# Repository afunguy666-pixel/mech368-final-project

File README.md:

# MECH 368 mobile robot starter

[中文版 / Chinese](README.zh-CN.md)

The direct-wired car uses four reflectance sensors on A0–A3, two LM393 obstacle
inputs and a DRV8833. Two Nano 33 BLE Sense Rev2 boards run `firmware/robot`
and `firmware/remote`. The remote sends heartbeats and accepts `e` over USB
serial to request an E-stop. With a fresh link, swipe UP on the car to calibrate
and start. After an E-stop, any new swipe on the car clears the latch. Wait for
a fresh heartbeat and swipe UP to drive. DOWN stops active navigation locally.

The remote forwards 10 Hz pose telemetry to a receive-only Windows recorder. An
optional normally-open handheld stop button connects D2 to ground. Build the
paired sketches with the project compile script for credit-aware BLE writes.
[Recorder, teach/live examples and bench results (Chinese)](docs/TELEMETRY.zh-CN.md)
· [Tilt steering, low-battery LED and heat map (Chinese)](docs/GESTURE_BATTERY_HEATMAP.zh-CN.md)

See [BLE protocol and bench checklist](docs/BLE_PROTOCOL.md) for the exact wire
format, timing, setup API blocking limitations and unperformed hardware tests.

| Path | Purpose |
| --- | --- |
| `firmware/robot/` | Direct-wired autonomous car, BLE watchdog, local recovery and motor enable |
| `firmware/remote/` | Remote sketch; integration point for pose estimation, BLE, and the E-stop request |
| `libraries/Mech368BLE/` | Portable packet codec, receiver and remote ACK tracking |
| `libraries/Mech368Safety/` | Portable state machine shared with the host test |
| `libraries/Mech368Line/` | Portable IR sensing, navigation, kinematics and odometry |
| `libraries/Mech368Tracker/` | Nano sensor and motor adapter shared by the car and standalone example. [Wiring and tuning](docs/LINE_FOLLOWING.md) |
| `tests/` | Deterministic host assertions for watchdog and E-stop behavior |
| `.github/workflows/ci.yml` | Independent host-test, firmware-simulator and board-compile jobs; no uploads to boards |

## Run locally

On Linux/macOS, or in a Windows Bash environment with the tools on PATH:

```sh
bash scripts/test-host.sh

# Requires Arduino CLI 1.3.1 on PATH (same toolchain CI uses).
arduino-cli core update-index
arduino-cli core install arduino:mbed_nano@4.6.0
arduino-cli lib install ArduinoBLE@2.1.1 Arduino_APDS9960@1.0.4 Arduino_BMI270_BMM150@1.2.4
bash scripts/compile-firmware.sh
```

The host test requires a C++11 compiler; set `CXX` if necessary. Compile only:
neither script flashes hardware. Arduino's [Rev2 manual](https://docs.arduino.cc/tutorials/nano-33-ble-sense-rev2/cheat-sheet/)
identifies the Mbed OS Nano package. The build target is `arduino:mbed_nano:nano33ble`.

## Implement and verify on the bench

1. **BLE and pose steering.** Verify the two actual boards and confirm which
   endpoint advertises. Measure BLE processing latency, including synchronous setup calls. Map
   calibrated remote roll and pitch to linear and angular velocity. Review the implemented
   command units, bounds, packet format and sequence/session handling. Validate
   type, size, version, bounds, and freshness before refreshing the watchdog;
   cached, malformed, duplicated or stale packets must not extend it. Treat
   reported disconnects immediately, and implement the required link-loss LED on
   each device (including detection of a stale peer on the remote).
2. **Motor inhibition and timing.** The state machine expires at 450 ms after
   the last new valid motion packet, leaving 50 ms for scheduling and output
   latency. That is not a hardware timing claim. With motors electrically
   isolated first, capture the last accepted packet and verified zero/disable
   output and demonstrate an end-to-end delay no longer than 500 ms under
   worst observed polling load. Test no packets at startup, packet silence,
   invalid traffic, abrupt disconnect and reconnect. Confirm actual motor
   driver polarity, disable behavior and electrical defaults before connecting
   motor power. All drive modes must share the same output gate.
3. **Emergency stop.** Show that a valid remote E-stop takes precedence over
   motion and a simultaneous recovery gesture, stays latched across a
   disconnect, and ignores further drive commands. Generate a new local
   APDS-9960 gesture event to clear the latch; confirm motion is still blocked
   until another good command arrives after recovery. The latch here is
   RAM-only. Verify startup/reset leaves physical outputs disabled; define
   a deliberate re-arm strategy before allowing motors to operate after reset.
4. **Remaining course hardware.** Verify the well-marked low-battery
   indicator and its threshold on your pack. Characterize wheel direction
   and encoder scaling, validate differential steering, and then test IR
   track following, obstacle avoidance, IMU/odometry pose tracking, and mapping
   against the course handout. Start motor tests with wheels clear of the
   bench and a safe independent means to cut power. Log measurements and
   observed behavior rather than treating compilation as acceptance.

## Firmware-in-the-loop simulator

Run the **unmodified** `robot.ino` and `remote.ino` on two virtual boards with a
simulated BLE radio, plus a virtual vehicle (motors, encoders, line sensors,
ultrasonic, IMU, gestures, battery, temperature) on the handout's field map, using only Bash and a
C++17 compiler:

```sh
bash scripts/run-fw-sim.sh                   # all scenarios
bash scripts/run-fw-sim.sh estop_latch       # one scenario with full log
bash scripts/run-fw-sim.sh --seeds 20 link_stability
```

Each run writes an interactive HTML replay plus CSV/log files to `build/fwsim/`.
Wiring, geometry and the course are text files in `sim/vehicles/` and
`sim/worlds/`; scenarios are C++ files in `sim/fwsim/scenarios/`. See
[docs/SIMULATOR.md](docs/SIMULATOR.md) for the API, the models, their limits,
and the current findings on the Phase 1 link timing.

| Path | Purpose |
| --- | --- |
| `sim/fwsim/hostduino/` | Host stand-ins for Arduino core, ArduinoBLE, BMI270/BMM150 IMU, APDS-9960, HS300x |
| `sim/fwsim/` | Virtual boards, radio, vehicle/world models, replay viewer, scenarios |
| `sim/examples/line_follower/` | Demo sketch (not course firmware) driving the virtual vehicle |
| `sim/examples/line_tracker/` | Standalone navigation example. Use `robot_track_cones` to exercise both course sketches together. |

## Software-in-the-loop (SIL) simulator

Run the host tests and generate five CSV traces without an Arduino, BLE hardware,
Python, or network access:

```sh
bash scripts/run-sil.sh
```

The traces go to `build/sil/`; pass a directory as the first argument to change
the destination. Use `CXX` to select a C++11 compiler. Run from Bash (for example,
Git Bash or WSL on Windows with a compiler on PATH). The CI host job also runs
this command; the existing firmware compilation remains independent.

Optional, with Python and matplotlib available, generate `tracking.png` and
`watchdog.png` from the CSV directory:

```sh
python sim/plot.py build/sil
```

The simulator advances a **virtual clock in 10 ms steps**, without sleeping.
A scripted remote generates commands every 50 ms. It passes correctly encoded
frames through an in-process queue with a fixed 20 ms delivery delay and a
scripted drop interval. The real portable `Receiver` and its `MotionSafety`
instance gate command values before the kinematic model consumes them.
Challenge/status is sampled instantly by the scripted remote; the simulator
does not emulate the actual BLE stack, timings, link budget, or remote firmware.

| CSV | What the test checks |
| --- | --- |
| `straight.csv` | Ideal straight motion: 0.50 m in 2 s after first accepted command; both estimators agree to within encoder resolution. |
| `turn90.csv` | One second straight (0.25 m), then a one-second pivot at 1.571 rad/s: near 90° without further translation. |
| `sensor_error.csv` | Straight/pivot/straight with fixed seed 368, opposite 2% wheel scale biases, bounded encoder/gyro noise, and fixed gyro bias. The test checks repeatability and nonzero finite error rather than assuming fusion wins. |
| `watchdog.csv` | While still virtually connected, commands go to zero at 970 ms (520 ms last accepted + 450 ms). A fresh frame restores control at 1070 ms. Explicit disconnect at 1300 ms zeros commands immediately; reconnect at 1450 ms remains blocked until a fresh frame at 1470 ms. |
| `estop.csv` | E-stop at 320 ms sets both wheel commands to zero and survives disconnect/reconnect. A synthetic **local** gesture at 900 ms clears the latch but leaves commands zero until the fresh frame at 920 ms. |

Each row records the receiver state, the gated chassis command (mm/s and
mrad/s), wheel commands (rad/s), and three XY/yaw poses (m and rad). Poses are
at the timestamp before applying its command to the next 10 ms interval; yaw
is unwrapped. Event labels mark packet delivery/drop, watchdog expiry,
disconnect, reconnect, E-stop, and local recovery.

The virtual geometry is a 0.10 m track width and 0.020 m wheel radius, with 1024
counts per wheel revolution. These and the noise/bias parameters are grouped in
`sil::Config` (`sim/Simulation.h`) and can be supplied to `sil::run`. Default CSVs
use the in-code defaults. Encoder deltas come from successive rounded cumulative
counts so small increments are not repeatedly rounded away. Ground
truth is ideal differential-drive motion without slip, inertia, or braking
dynamics. Both estimators use the same observed wheel increments for distance;
encoder-only yaw comes from their difference, while fused yaw increments are a
fixed 10% encoder / 90% gyro blend. The weights and biases are illustrative,
not calibrated. A lower error here does not establish performance on the
actual robot or guarantee the blend helps under other conditions.

SIL validates the gating and model under the given scripts, not hardware
stopping behavior. Still verify the actual BLE exchange, loop and driver
latency, E-stop/re-arm I/O, encoder scaling, gyro calibration, and mechanical
behavior on a bench before applying motor power for a loaded test.

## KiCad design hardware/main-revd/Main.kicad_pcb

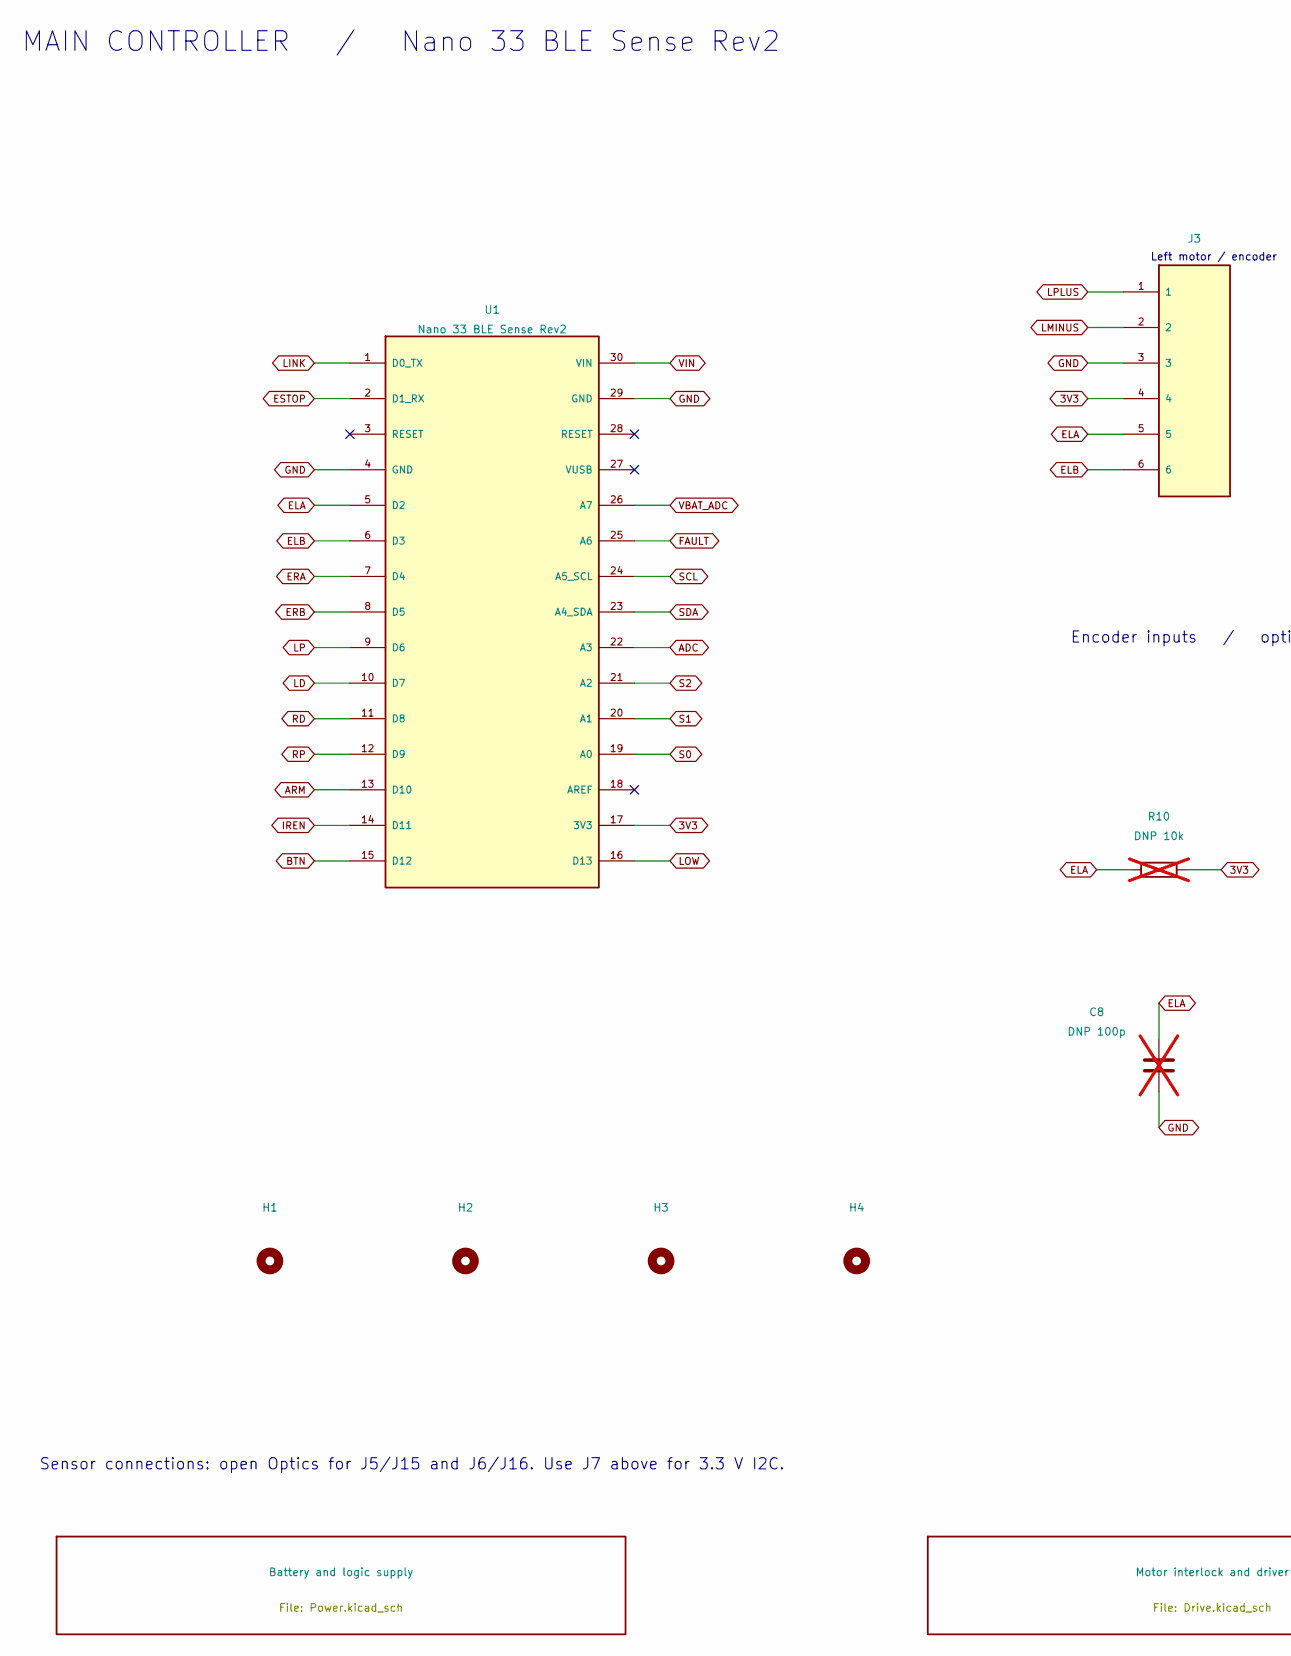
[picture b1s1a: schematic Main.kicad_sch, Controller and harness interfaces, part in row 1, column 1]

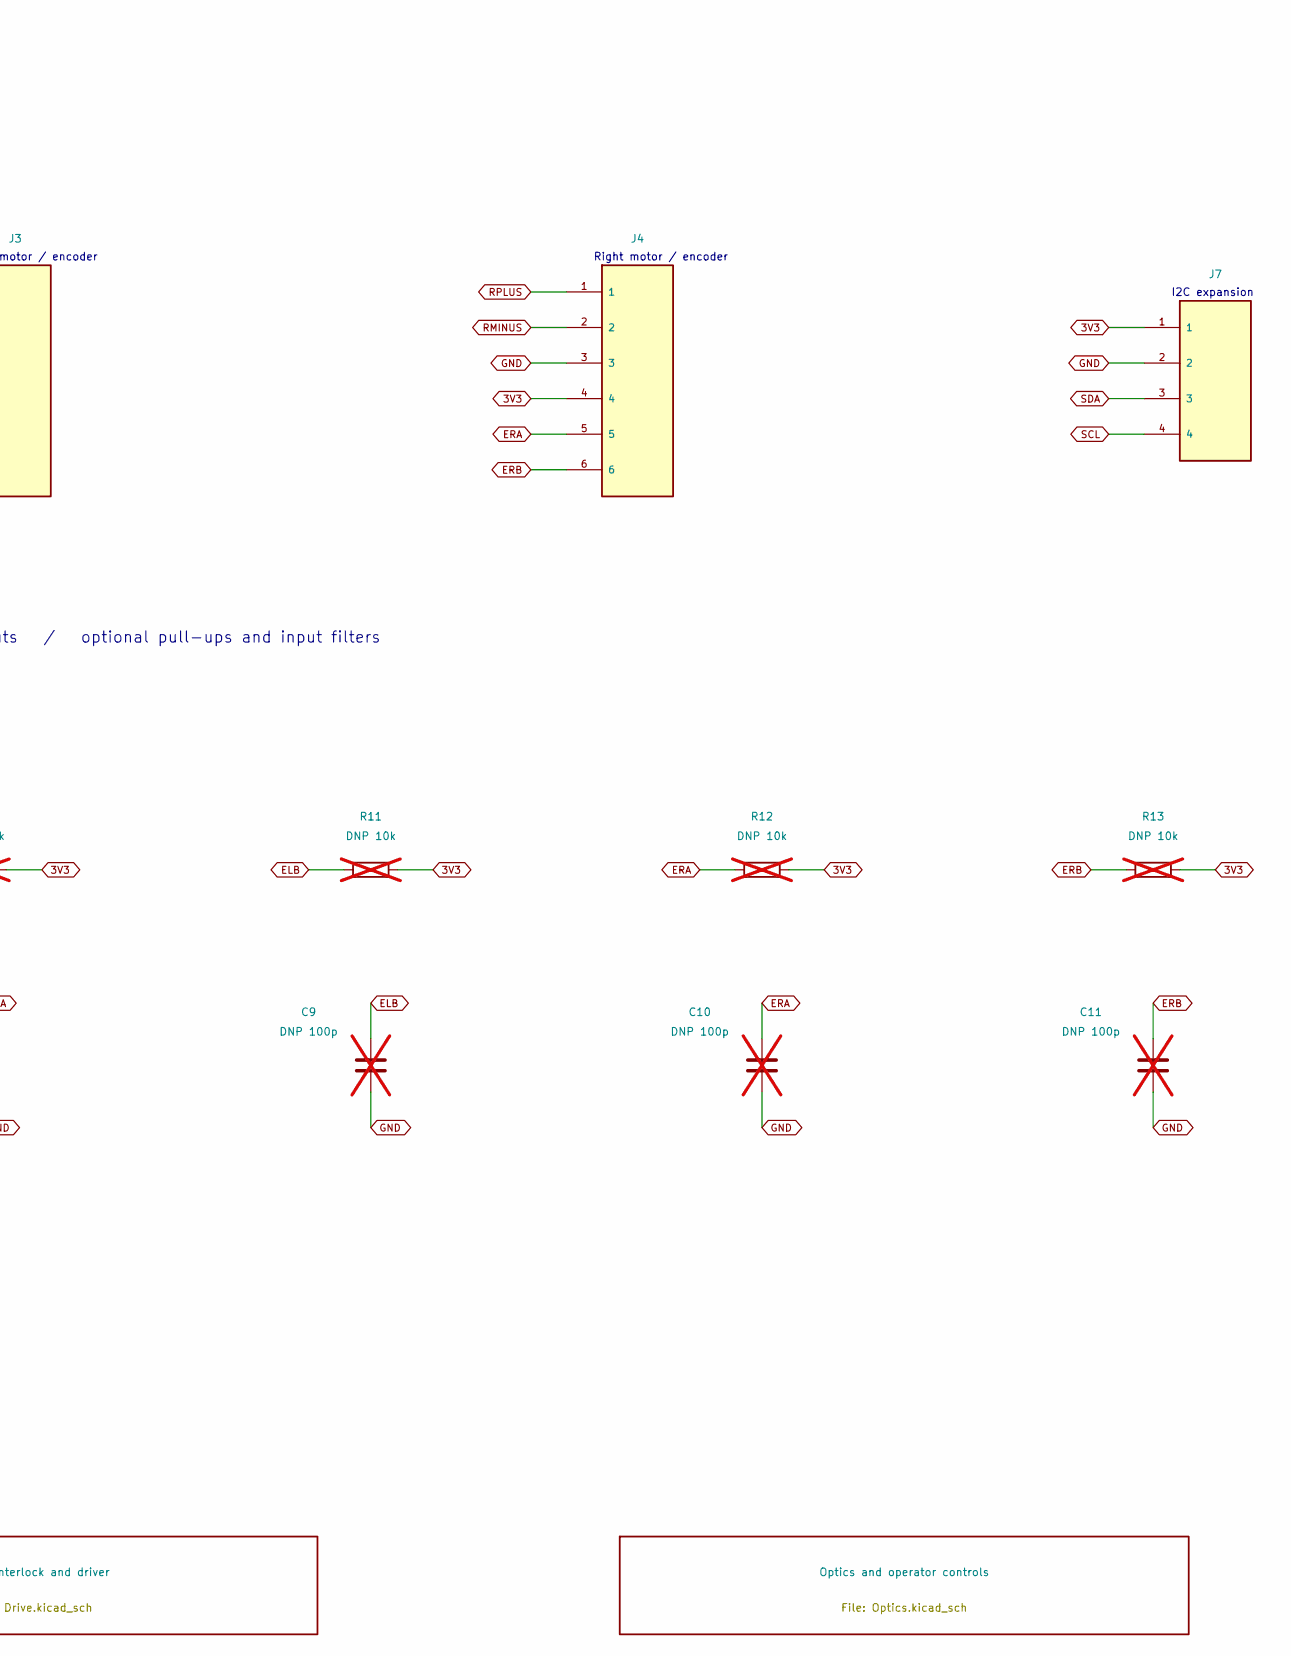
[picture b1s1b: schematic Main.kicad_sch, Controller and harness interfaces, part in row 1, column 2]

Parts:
C8, C9, C10, C11: DNP 100p; C_0805_2012Metric; not fitted
H1, H2, H3, H4: MountingHole_3.2mm_M3
J3, J4: PH; JST_PH_B6B-PH-K_1x06_P2.00mm_Vertical
J7: I2C; PinHeader_1x04_P2.54mm_Vertical
R10, R11, R12, R13: DNP 10k; R_Axial_DIN0207_L6.3mm_D2.5mm_P10.16mm_Horizontal; not fitted
U1: Nano 33 BLE Sense Rev2; Arduino_Nano

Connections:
3V3: J3.4, J4.4, J7.1, R10.2, R11.2, R12.2, R13.2, U1.17 (3V3); also elsewhere on the board
ADC: U1.22 (A3); also elsewhere on the board
ARM: U1.13 (D10); also elsewhere on the board
BTN: U1.15 (D12); also elsewhere on the board
ELA: C8.1, J3.5, R10.1, U1.5 (D2)
ELB: C9.1, J3.6, R11.1, U1.6 (D3)
ERA: C10.1, J4.5, R12.1, U1.7 (D4)
ERB: C11.1, J4.6, R13.1, U1.8 (D5)
ESTOP: U1.2 (D1_RX); also elsewhere on the board
FAULT: U1.25 (A6); also elsewhere on the board
GND: C8.2, C9.2, C10.2, C11.2, J3.3, J4.3, J7.2, U1.4 (GND), U1.29 (GND); also elsewhere on the board
IREN: U1.14 (D11); also elsewhere on the board
LD: U1.10 (D7); also elsewhere on the board
LINK: U1.1 (D0_TX); also elsewhere on the board
LMINUS: J3.2; also elsewhere on the board
LOW: U1.16 (D13); also elsewhere on the board
LP: U1.9 (D6); also elsewhere on the board
LPLUS: J3.1; also elsewhere on the board
RD: U1.11 (D8); also elsewhere on the board
RMINUS: J4.2; also elsewhere on the board
RP: U1.12 (D9); also elsewhere on the board
RPLUS: J4.1; also elsewhere on the board
S0: U1.19 (A0); also elsewhere on the board
S1: U1.20 (A1); also elsewhere on the board
S2: U1.21 (A2); also elsewhere on the board
SCL: J7.4, U1.24 (A5_SCL)
SDA: J7.3, U1.23 (A4_SDA)
VBAT_ADC: U1.26 (A7); also elsewhere on the board
VIN: U1.30 (VIN); also elsewhere on the board

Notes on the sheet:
MAIN CONTROLLER / Nano 33 BLE Sense Rev2
Left motor / encoder
Right motor / encoder
I2C expansion
Encoder inputs / optional pull-ups and input filters
Sensor connections: open Optics for J5/J15 and J6/J16. Use J7 above for 3.3 V I2C.

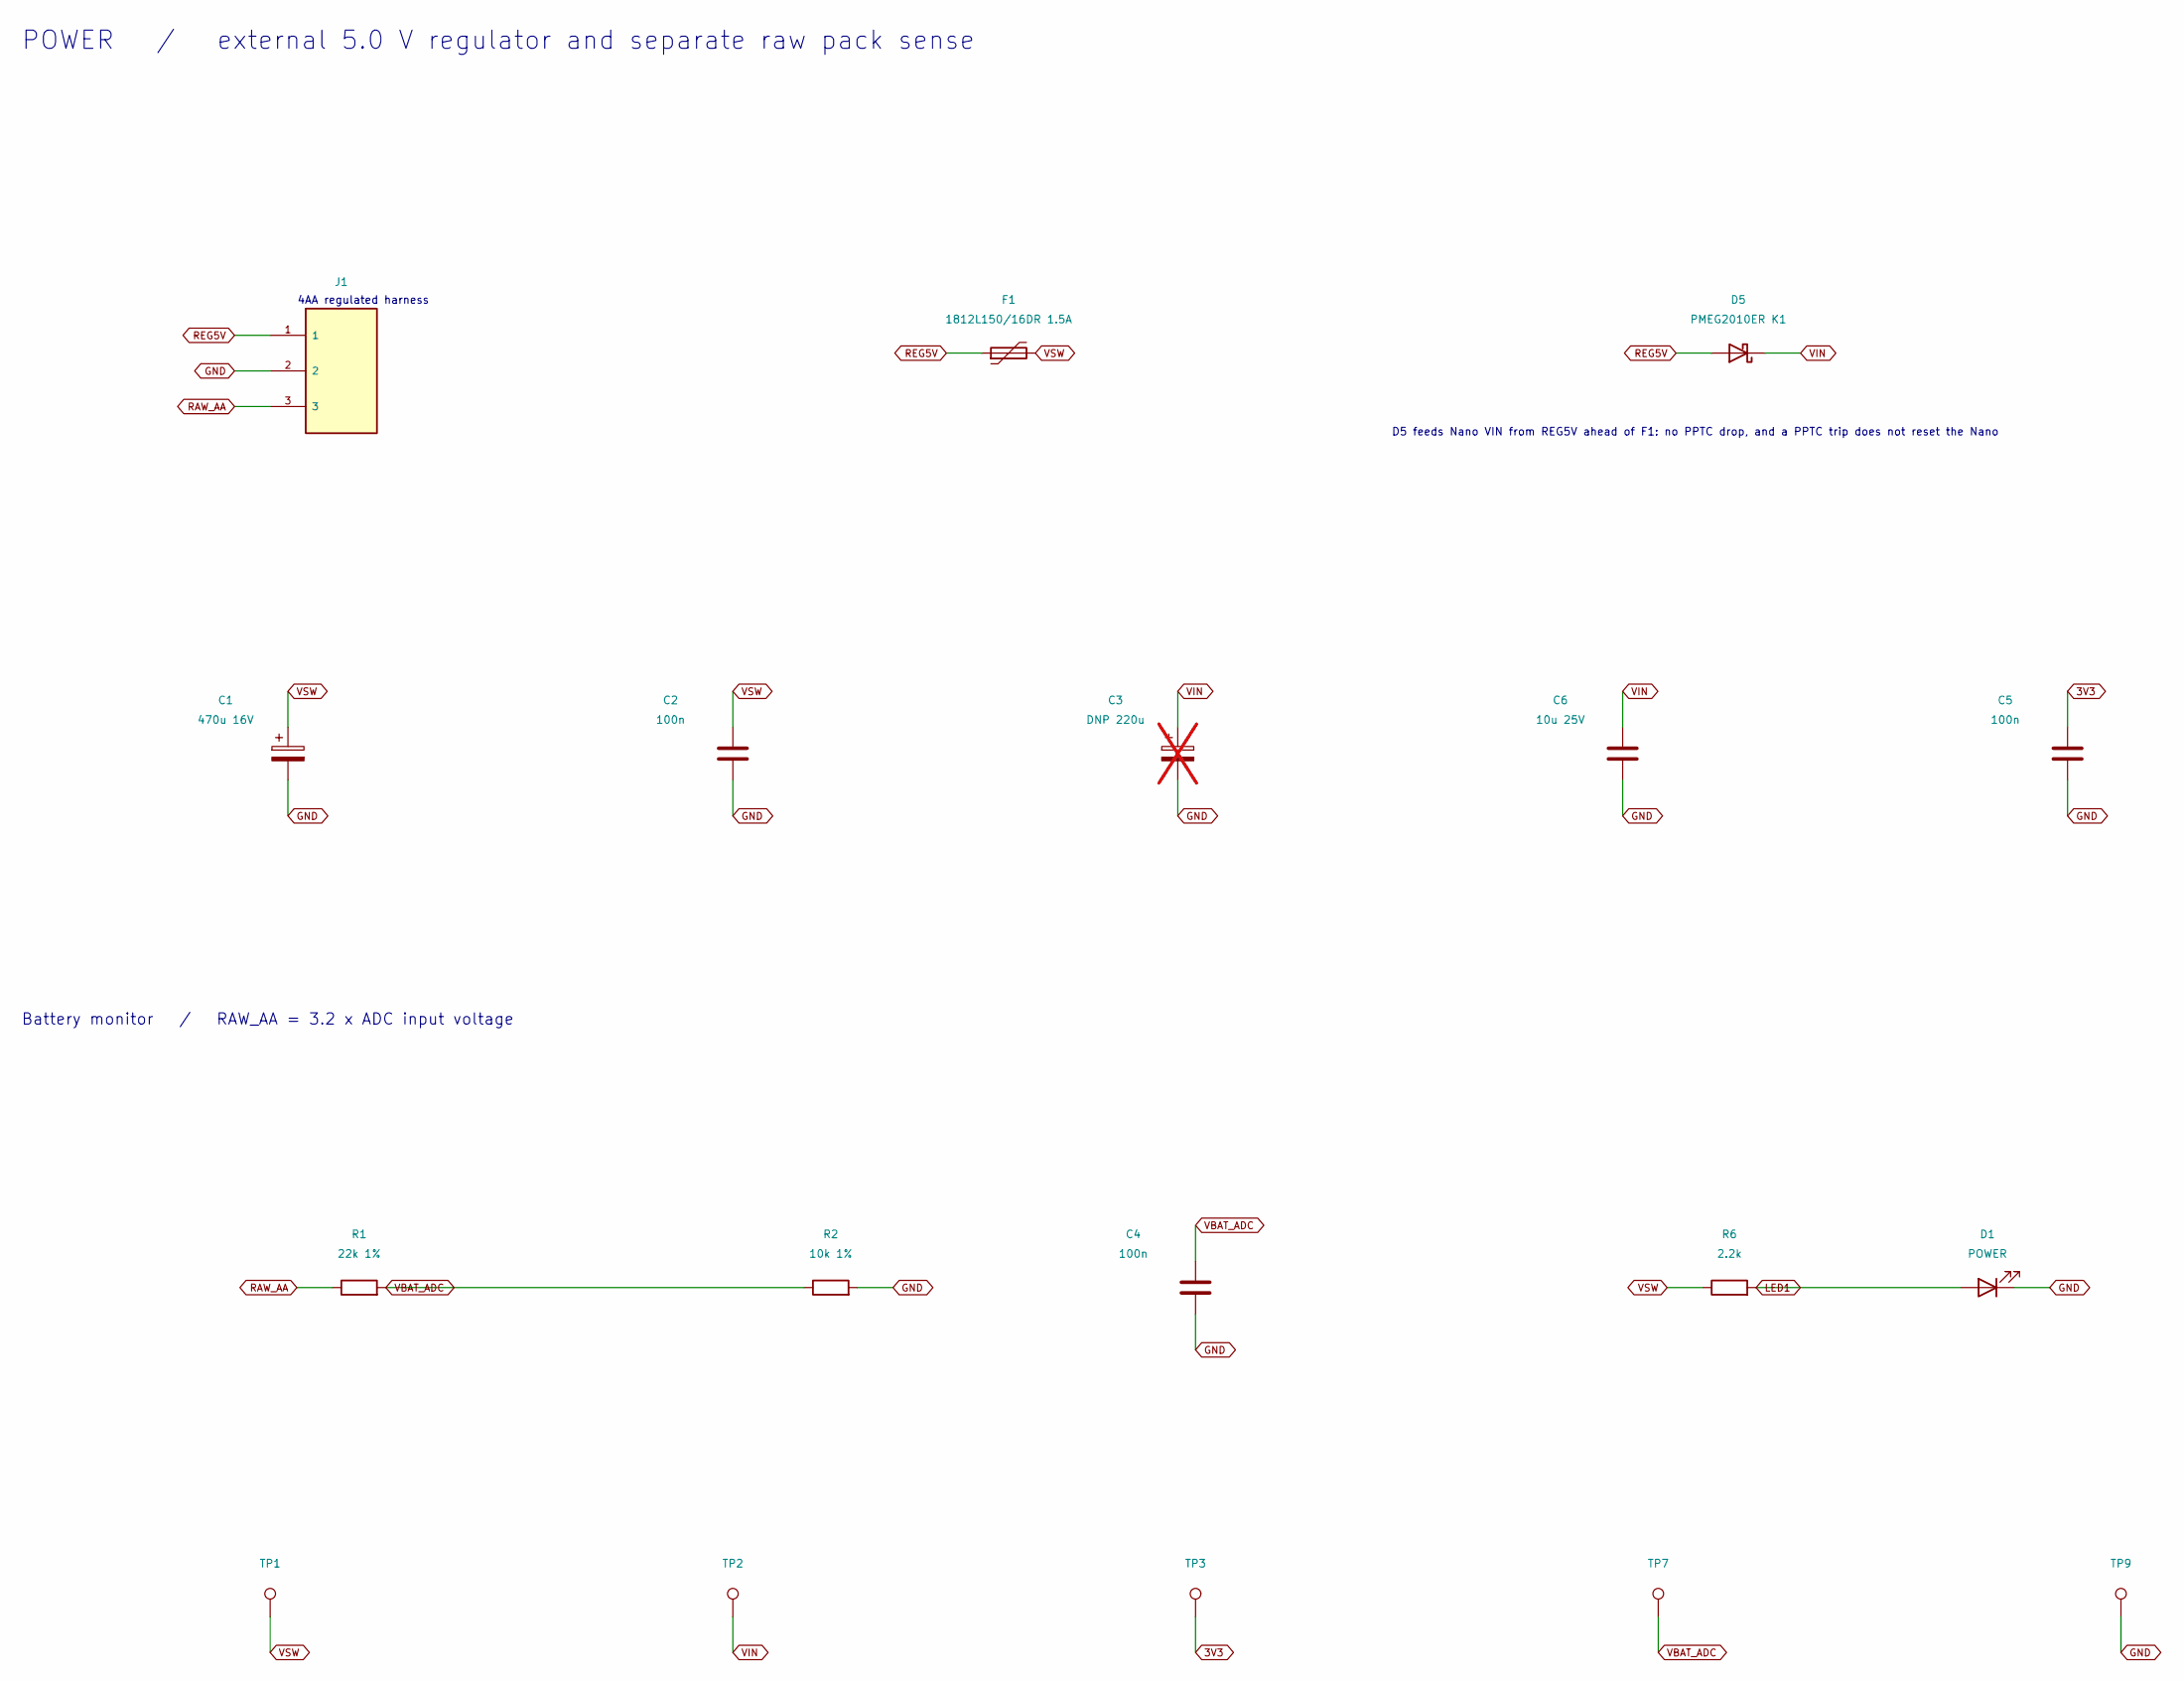
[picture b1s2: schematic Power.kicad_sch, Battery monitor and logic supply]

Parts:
C1: 470u 16V; CP_Radial_D8.0mm_P3.50mm
C2, C4, C5: 100n; C_0805_2012Metric
C3: DNP 220u; CP_Radial_D6.3mm_P2.50mm; not fitted
C6: 10u 25V; C_0805_2012Metric
D1: POWER; LED_D3.0mm
D5: PMEG2010ER K1; Nexperia_CFP3_SOD-123W
F1: 1812L150/16DR 1.5A; Fuse_1812_4532Metric
J1: XH; JST_XH_B3B-XH-A_1x03_P2.50mm_Vertical
R1: 22k 1%; R_Axial_DIN0207_L6.3mm_D2.5mm_P10.16mm_Horizontal
R2: 10k 1%; R_Axial_DIN0207_L6.3mm_D2.5mm_P10.16mm_Horizontal
R6: 2.2k; R_Axial_DIN0207_L6.3mm_D2.5mm_P10.16mm_Horizontal
TP1: VSW; TestPoint_Pad_D1.5mm
TP2: VIN; TestPoint_Pad_D1.5mm
TP3: 3V3; TestPoint_Pad_D1.5mm
TP7: VBAT_ADC; TestPoint_Pad_D1.5mm
TP9: GND; TestPoint_Pad_D1.5mm

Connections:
3V3: C5.1, TP3.1; also elsewhere on the board
GND: C1.2, C2.2, C3.2, C4.2, C5.2, C6.2, D1.1 (K), J1.2, R2.2, TP9.1; also elsewhere on the board
LED1: D1.2 (A), R6.2
RAW_AA: J1.3, R1.1
REG5V: D5.2 (A), F1.1, J1.1
VBAT_ADC: C4.1, R1.2, R2.1, TP7.1; also elsewhere on the board
VIN: C3.1, C6.1, D5.1 (K), TP2.1; also elsewhere on the board
VSW: C1.1, C2.1, F1.2, R6.1, TP1.1; also elsewhere on the board

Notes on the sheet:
POWER / external 5.0 V regulator and separate raw pack sense
4AA regulated harness
D5 feeds Nano VIN from REG5V ahead of F1: no PPTC drop, and a PPTC trip does not reset the Nano
Battery monitor / RAW_AA = 3.2 x ADC input voltage

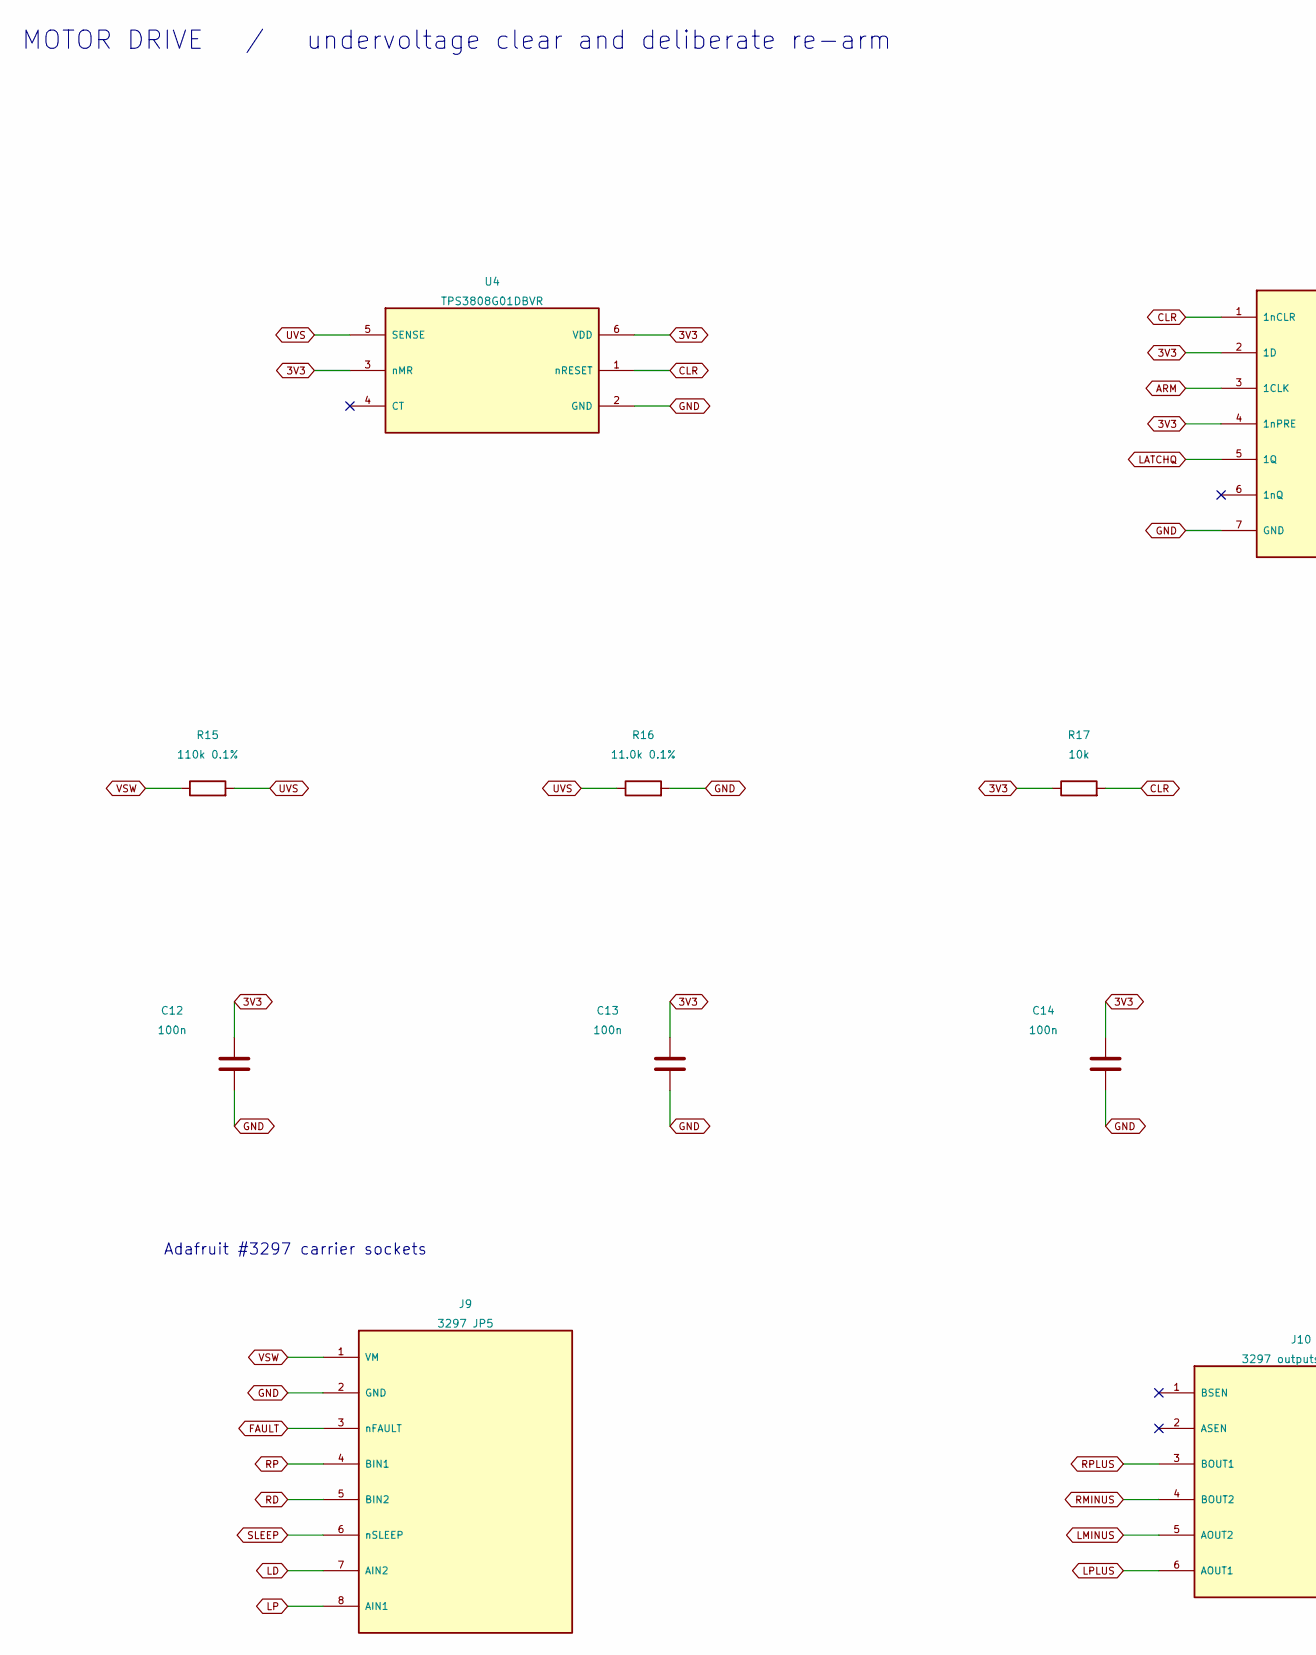
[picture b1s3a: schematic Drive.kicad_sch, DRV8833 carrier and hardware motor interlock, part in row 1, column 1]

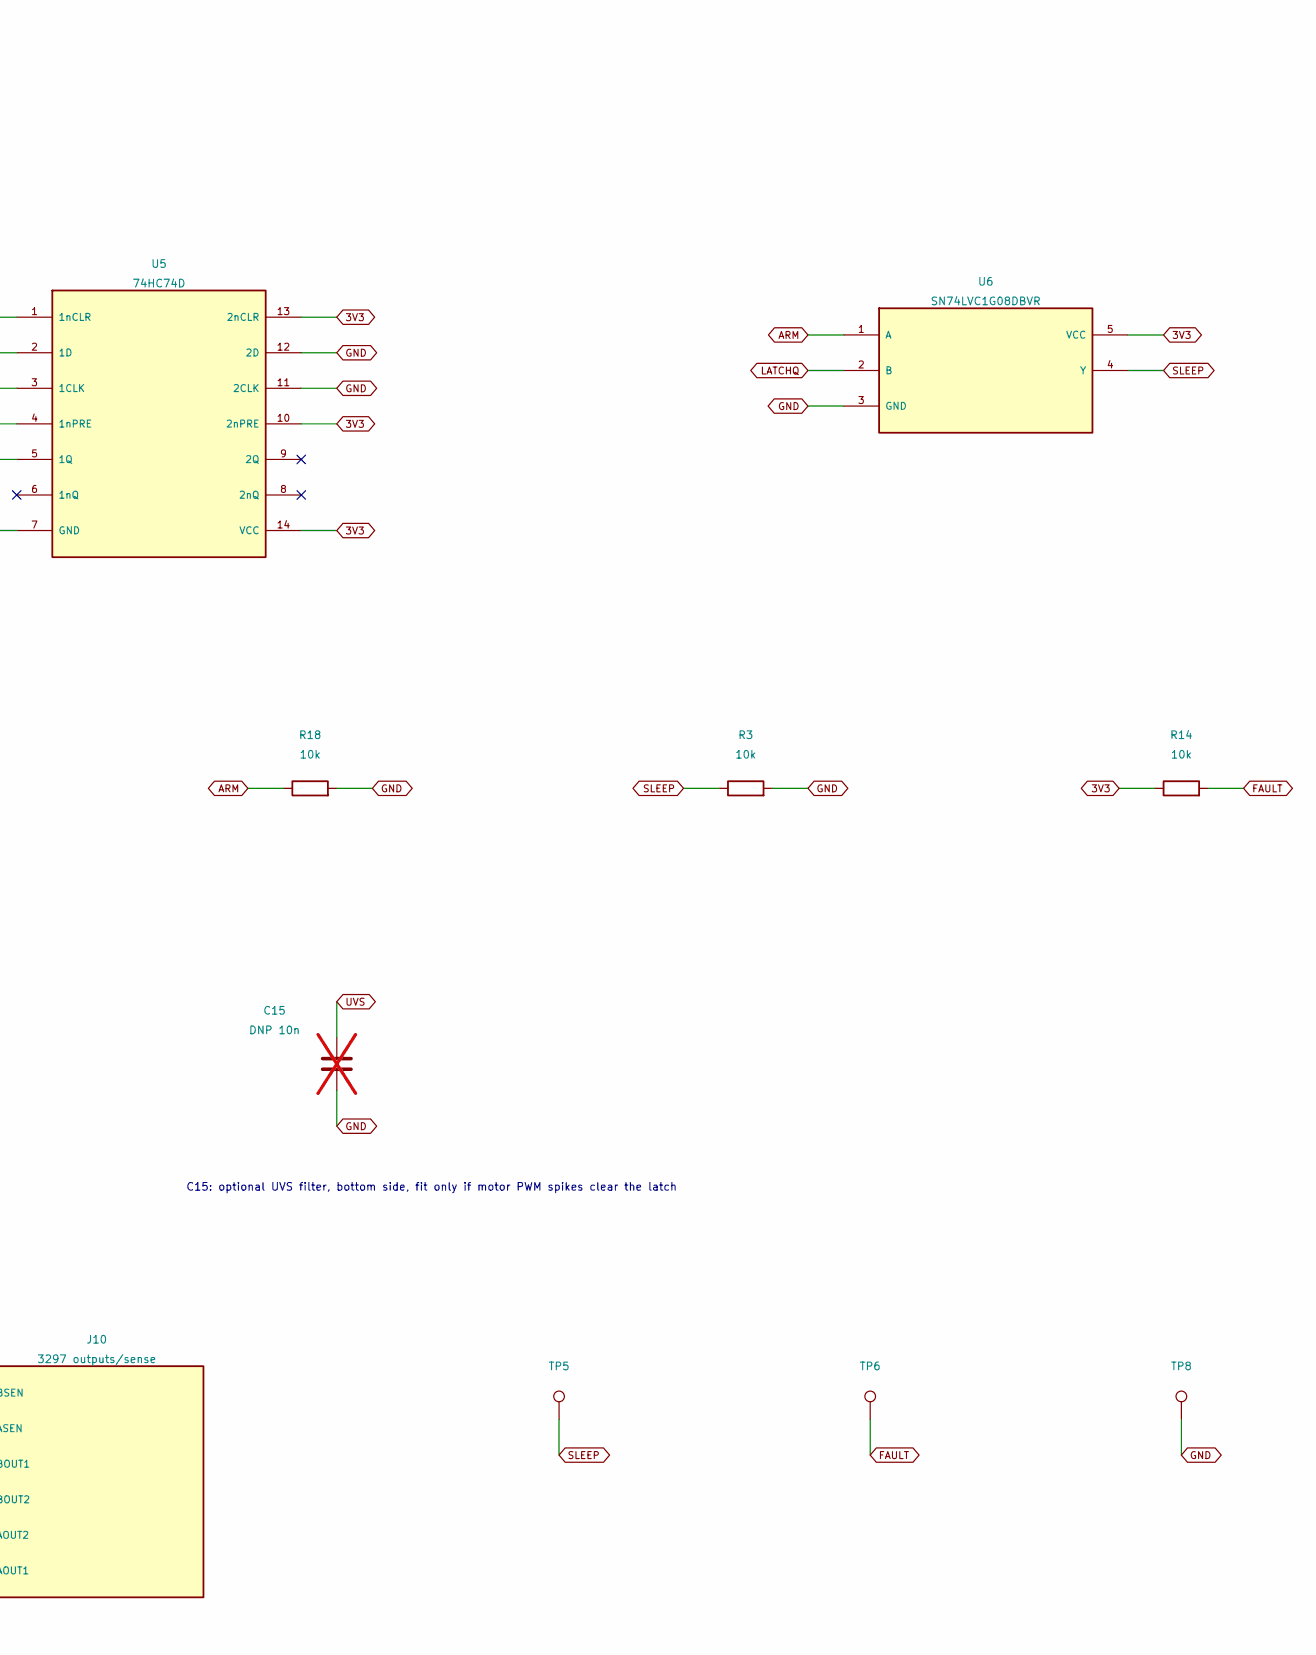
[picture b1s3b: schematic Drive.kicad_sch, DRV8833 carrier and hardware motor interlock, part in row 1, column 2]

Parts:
C12, C13, C14: 100n; C_0805_2012Metric
C15: DNP 10n; C_0805_2012Metric; not fitted
J9: 3297 JP5; PinSocket_1x08_P2.54mm_Vertical
J10: 3297 outputs/sense; PinSocket_1x06_P2.54mm_Vertical
R3, R14, R17, R18: 10k; R_Axial_DIN0207_L6.3mm_D2.5mm_P10.16mm_Horizontal
R15: 110k 0.1%; R_0805_2012Metric
R16: 11.0k 0.1%; R_0805_2012Metric
TP5: SLEEP; TestPoint_Pad_D1.5mm
TP6: FAULT; TestPoint_Pad_D1.5mm
TP8: GND; TestPoint_Pad_D1.5mm
U4: TPS3808G01DBVR; SOT-23-6
U5: 74HC74D; SOIC-14_3.9x8.7mm_P1.27mm
U6: SN74LVC1G08DBVR; SOT-23-5

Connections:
3V3: C12.1, C13.1, C14.1, R14.1, R17.1, U4.3 (nMR), U4.6 (VDD), U5.2 (1D), U5.4 (1nPRE), U5.10 (2nPRE), U5.13 (2nCLR), U5.14 (VCC), U6.5 (VCC); also elsewhere on the board
ARM: R18.1, U5.3 (1CLK), U6.1 (A); also elsewhere on the board
CLR: R17.2, U4.1 (nRESET), U5.1 (1nCLR)
FAULT: J9.3 (nFAULT), R14.2, TP6.1; also elsewhere on the board
GND: C12.2, C13.2, C14.2, C15.2, J9.2 (GND), R3.2, R16.2, R18.2, TP8.1, U4.2 (GND), U5.7 (GND), U5.11 (2CLK), U5.12 (2D), U6.3 (GND); also elsewhere on the board
LATCHQ: U5.5 (1Q), U6.2 (B); also elsewhere on the board
LD: J9.7 (AIN2); also elsewhere on the board
LMINUS: J10.5 (AOUT2); also elsewhere on the board
LP: J9.8 (AIN1); also elsewhere on the board
LPLUS: J10.6 (AOUT1); also elsewhere on the board
RD: J9.5 (BIN2); also elsewhere on the board
RMINUS: J10.4 (BOUT2); also elsewhere on the board
RP: J9.4 (BIN1); also elsewhere on the board
RPLUS: J10.3 (BOUT1); also elsewhere on the board
SLEEP: J9.6 (nSLEEP), R3.1, TP5.1, U6.4 (Y)
UVS: C15.1, R15.2, R16.1, U4.5 (SENSE)
VSW: J9.1 (VM), R15.1; also elsewhere on the board

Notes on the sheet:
MOTOR DRIVE / undervoltage clear and deliberate re-arm
C15: optional UVS filter, bottom side, fit only if motor PWM spikes clear the latch
Adafruit #3297 carrier sockets
